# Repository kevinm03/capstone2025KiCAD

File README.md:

# LANL100kTankKiCAD
LANL 100k tank grab sampling capstone project KiCAD, schematics, and PCB files.

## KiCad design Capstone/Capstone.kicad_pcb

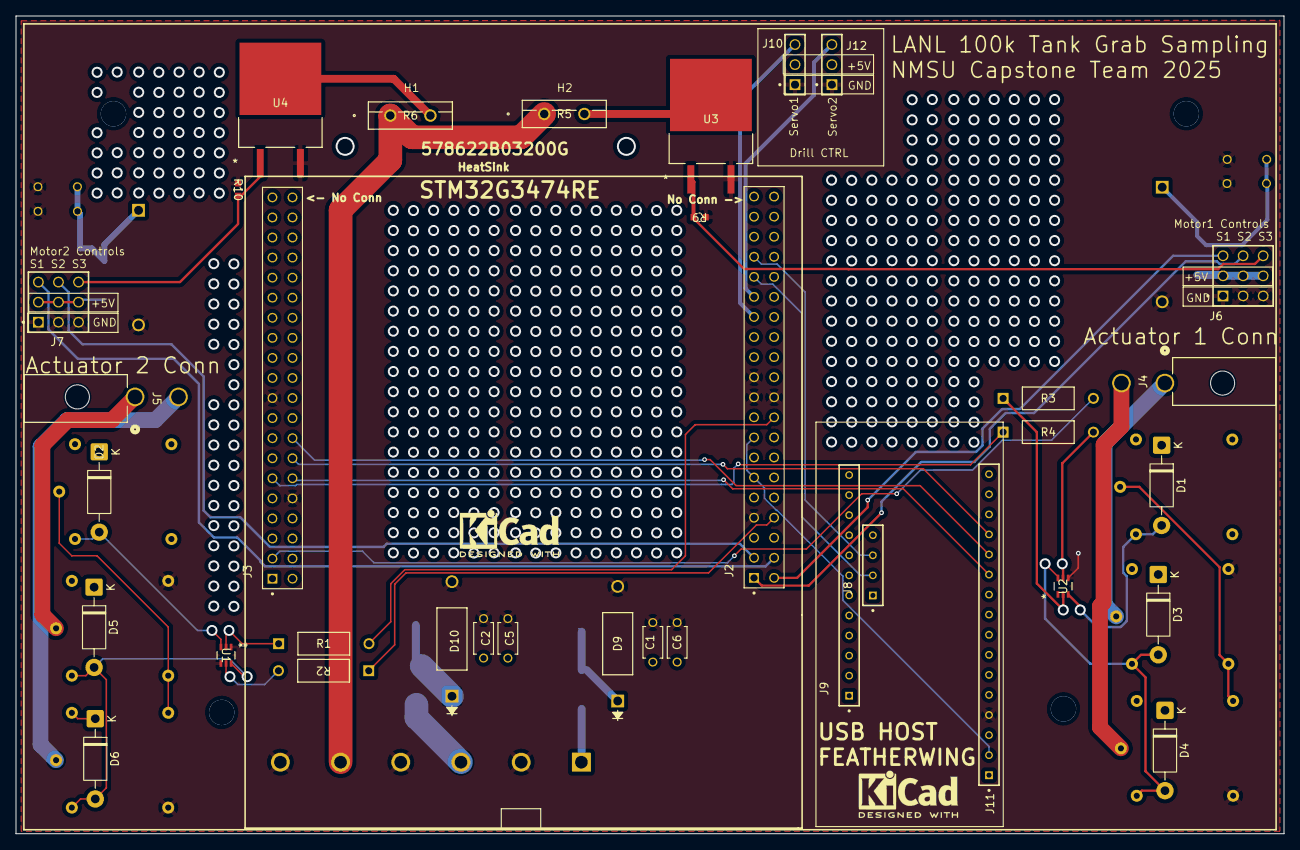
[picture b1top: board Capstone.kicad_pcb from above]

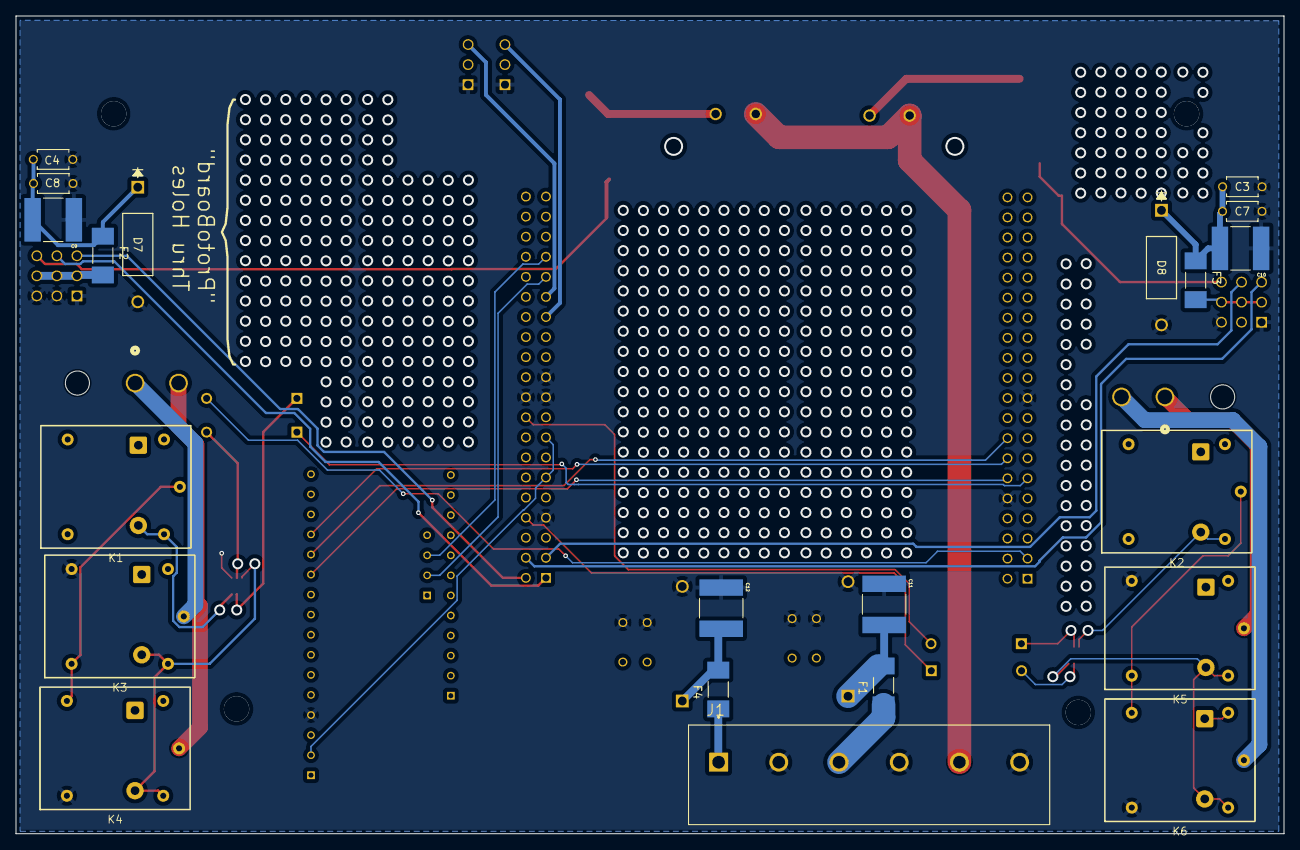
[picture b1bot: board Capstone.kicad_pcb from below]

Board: 6 copper layers, 160.5 x 103.5 mm, 58 parts (21 on the bottom side), 42 nets.

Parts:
C1, C2, C3, C4: FG28X7R1H104KNT06; CAPRB500W50L400T250H550
C5, C6, C7, C8: FG18X5R1E106MRT06; CAPRB500W50L400T250H550
C9, C10, C11, C12: KRM55WC71E107MH13L; CAPC6153X670N
D1, D2, D3, D4, D5, D6: 1N4001; D_DO-41_SOD81_P10.16mm_Horizontal
D7, D8, D9: SA6.0A; SASeries_LTF
D10: SA15A; SASeries_LTF
F1: 0679L9200-05; FUSC6125X279N
F2, F3: 0679L1000-05; FUSC6125X279N
F4: 0679H3000-05; FUSC6125X279N
H1, H2: Heatsink
J1: CUI_TB005_-762-06BE
J2, J3: PPTC202LFBN-RC; TE_2-215307-0
J4, J5: 1724480002; CONN_SD-172448-0000_02_MOL
J6, J7: TSW-103-07-G-T; SAMTEC_TSW-103-07-G-T
J8: TS-104-G-AA; SAMTEC_TS-104-G-AA
J9: TS-112-G-AA; SAMTEC_TS-112-G-AA
J10, J12: TSW-101-17-T-T; SAMTEC_TSW-101-17-T-T
J11: TS-116-G-A; SAMTEC_TS-116-G-A
K1, K2, K3, K4, K5, K6: J1071CS12VDC.36
R1, R2, R3, R4: CF14JT10K0; STA_CF14_STP
R5, R6: LTO050F10R00JTE3/TPAN0220J1R00K9; TO220_LTO_VIS
R9, R10: RC0603FR-0710KL; RC0603N_YAG
U1, U2: SSM6N7002KFU_LF; SOT-363 US6_TOS
U3, U4: BUK965R8-100E_118; SOT404_D2PAK_NEX

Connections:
+3V3: J2.11, J2.15, J11.02
+5V: C1.1, C3.2, C4.2, C6.1, C7.1, C8.1, C9.2, C10.2, C12.2, D7.1, D8.1, D9.1, F2.1, F3.1, F4.2, J2.5, J2.17, J8.04, J10.02, J12.02
+12V: C2.1, C5.1, C11.2, D1.1 (K), D2.1 (K), D3.1 (K), D4.1 (K), D5.1 (K), D6.1 (K), D10.1, F1.2, K1.1 (NO), K1.2 (Coil), K2.1 (NO), K2.2 (Coil), K3.2 (Coil), K4.2 (Coil), K5.2 (Coil), K6.2 (Coil)
+48V: J1.5, R5.1, R6.1
/ActuatorCTRL/Actuator1Neg: J4.2, K4.4 (Com)
/ActuatorCTRL/Actuator1Pos: J4.1, K3.4 (Com)
/ActuatorCTRL/Actuator1_Power: K1.4 (Com), K3.3 (NC), K4.1 (NO)
/ActuatorCTRL/Actuator2Neg: J5.2, K6.4 (Com)
/ActuatorCTRL/Actuator2Pos: J5.1, K5.4 (Com)
/ActuatorCTRL/Actuator2_Power: K2.4 (Com), K5.3 (NC), K6.1 (NO)
/ActuatorCTRL/K1Ctrl: D1.2 (A), K1.5 (Coil), U2.3 (DRAIN2)
/ActuatorCTRL/K2Ctrl: D2.2 (A), K2.5 (Coil), U1.3 (DRAIN2)
/ActuatorCTRL/K34Ctrl: D3.2 (A), D4.2 (A), K3.5 (Coil), K4.5 (Coil), U2.6 (DRAIN1)
/ActuatorCTRL/K56Ctrl: D5.2 (A), D6.2 (A), K5.5 (Coil), K6.5 (Coil), U1.6 (DRAIN1)
/ActuatorCTRL/actuator1_fwdrev: J2.8, R2.1
/ActuatorCTRL/actuator1_onoff: J2.18, R1.2
/ActuatorCTRL/actuator2_fwdrev: J3.11, R4.1
/ActuatorCTRL/actuator2_onoff: J3.3, R3.2
/STM32 &Headers/5VEXT: F4.1, J1.1
/STM32 &Headers/12VEXT: F1.1, J1.3
/STM32 &Headers/S1_motor1: J2.2, J6.03
/STM32 &Headers/S1_motor2: J2.4, J7.03
/STM32 &Headers/S2_motor1: J2.1, J6.06
/STM32 &Headers/S2_motor2: J2.3, J7.06
/STM32 &Headers/SERVO1_PWM: J2.27, J10.03
/STM32 &Headers/SERVO2_PWM: J2.29, J12.03
/STM32 &Headers/USB_CS: J2.31, J8.02
/STM32 &Headers/USB_IRQ: J2.33, J8.03
/STM32 &Headers/USB_MISO: J3.14, J11.13
/STM32 &Headers/USB_MOSI: J3.16, J11.12
/STM32 &Headers/USB_SCK: J3.12, J11.11
/Screw Motors/S3_motor1: J6.09, R9.2, U3.1 (G)
/Screw Motors/S3_motor2: J7.09, R10.2, U4.1 (G)
GND: C1.2, C2.2, C3.1, C4.1, C5.2, C6.2, C7.2, C8.2, C9.1, C10.1, C11.1, C12.1, D7.2, D8.2, D9.2, D10.2, J1.2, J1.4, J1.6, J2.7, J2.19, J2.20, J2.21, J3.10, J3.19, J6.01, J6.04, J6.07, J7.01, J7.04, J7.07, J10.01, J11.04, J12.01, K3.1 (NO), K4.3 (NC), K5.1 (NO), K6.3 (NC), R9.1, R10.1, U1.1 (SOURCE1), U1.4 (SOURCE2), U2.1 (SOURCE1), U2.4 (SOURCE2), U3.3 (S), U4.3 (S)
unnamed: F2.2, J6.02, J6.05, J6.08
unnamed: F3.2, J7.02, J7.05, J7.08
unnamed: R1.1, U1.2 (GATE1)
unnamed: R2.2, U1.5 (GATE2)
unnamed: R3.1, U2.2 (GATE1)
unnamed: R4.2, U2.5 (GATE2)
unnamed: R5.2, U3.2 (D)
unnamed: R6.2, U4.2 (D)

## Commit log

2025-11-18 Kicad files added
2025-11-18 Board outline and Step file created
2025-11-20 Added regen voltage clamping components & MCU model
2025-12-01 Added Actuator control circuitry with MOSFET's and Relays
2025-12-04 multiple sheets. Actuator controls
2025-12-04 Ref Des Updates
2025-12-04 Small changes, moving things around, renaming pins
2026-02-06 New components & Host shield
2026-02-07 USB Model
2026-02-11 Changed net-labels, modified pins
2026-02-14 Added decoupling capacitors, fuses, finalized pcb, needs routing
2026-02-16 Traces routed, gerber files generated
2026-02-17 GerberFiles ready
2026-02-27 Added roller motor on schematic and hierarchical sheet. No PCB update
2026-02-27 Diode protections added on H-Bridge
2026-03-06 Added models
